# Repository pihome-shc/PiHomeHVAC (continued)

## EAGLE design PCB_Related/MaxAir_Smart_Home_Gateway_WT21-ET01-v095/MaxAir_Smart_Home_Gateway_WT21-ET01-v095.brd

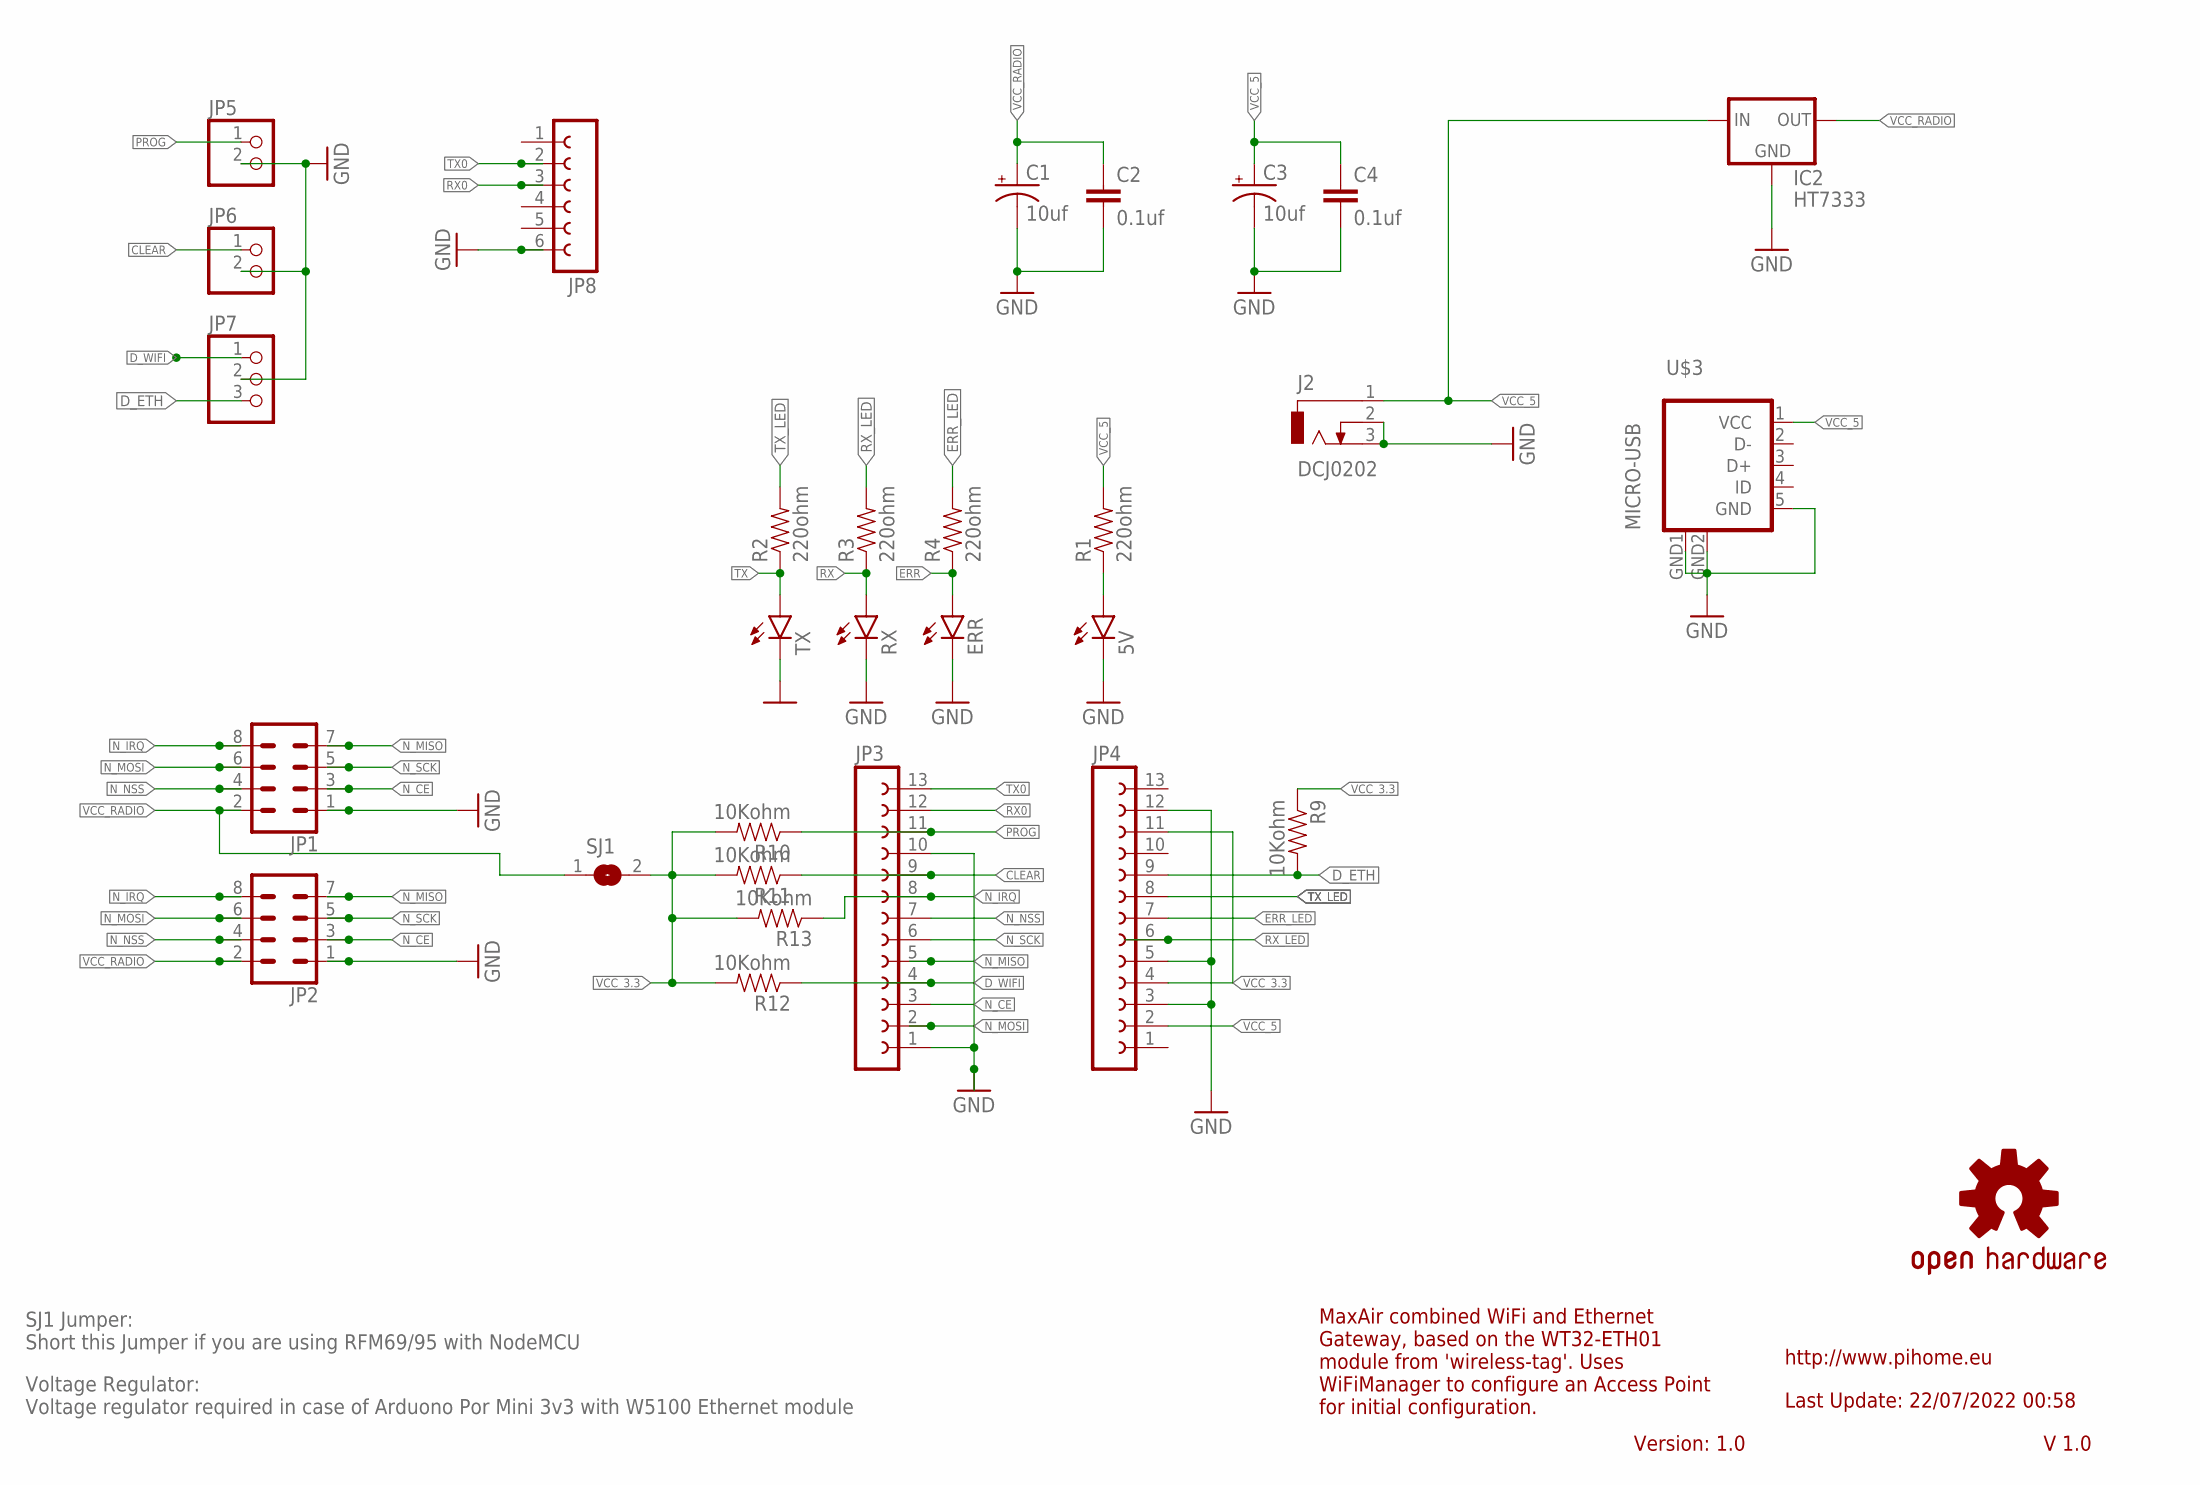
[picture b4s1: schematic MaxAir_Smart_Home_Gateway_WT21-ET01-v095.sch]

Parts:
5V: LED3MM
C1, C3: 10uf; CPOL-RADIAL-10UF-25V-KIT
C2, C4: 0.1uf; CAP-PTH-SMALL-KIT
ERR: LED3MM
IC2: HT7333; SOT-89
J2: DCJ0202
JP1, JP2: CONN_04X2; 2X4
JP3, JP4: FE13-1; FE13
JP5, JP6: PINHD-1X2; 1X02
JP7: PINHD-1X3; 1X03
JP8: FE06-1; FE06
LOGO1: OSHW-LOGOMINI; OSHW-LOGO-MINI
R1, R2, R3, R4: 220ohm; AXIAL-0.3
R9, R10, R11, R12, R13: 10Kohm; AXIAL-0.3
RX: LED3MM
SJ1: SJ
TX: LED3MM
U$3: MICRO-USB

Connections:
CLEAR: JP3.9, JP6.1, R11.P$1 (1)
D_ETH: JP4.9, JP7.3, R9.P$2 (2)
D_WIFI: JP3.4, JP7.1, R12.P$1 (1)
ERR: ERR.A, R4.P$1 (1)
ERR_LED: JP4.7, R4.P$2 (2)
GND: 5V.K (C), C1.2 (-), C2.2, C3.2 (-), C4.2, ERR.K (C), IC2.2 (GND), J2.2, J2.3, JP1.1, JP2.1, JP3.1, JP3.10, JP4.3, JP4.5, JP4.12, JP5.2, JP6.2, JP7.2, JP8.6, RX.K (C), TX.K (C), U$3.5 (GND), U$3.GND1 (GND), U$3.GND2 (GND)
unnamed: 5V.A, R1.P$1 (1)
N_CE: JP1.3, JP2.3, JP3.3
N_IRQ: JP1.8, JP2.8, JP3.8, R13.P$1 (1)
N_MISO: JP1.7, JP2.7, JP3.5
N_MOSI: JP1.6, JP2.6, JP3.2
N_NSS: JP1.4, JP2.4, JP3.7
N_SCK: JP1.5, JP2.5, JP3.6
PROG: JP3.11, JP5.1, R10.P$1 (1)
RX: R3.P$1 (1), RX.A
RX0: JP3.12, JP8.3
RX_LED: JP4.6, R3.P$2 (2)
TX: R2.P$1 (1), TX.A
TX0: JP3.13, JP8.2
TX_LED: JP4.8, R2.P$2 (2)
VCC_3.3: JP4.4, JP4.11, R9.P$1 (1), R10.P$2 (2), R11.P$2 (2), R12.P$2 (2), R13.P$2 (2), SJ1.2
VCC_5: C3.1 (+), C4.1, IC2.3 (IN), IC2.4 (IN), J2.1, JP4.2, R1.P$2 (2), U$3.1 (VCC)
VCC_RADIO: C1.1 (+), C2.1, IC2.1 (OUT), JP1.2, JP2.2, SJ1.1

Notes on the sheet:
http://www.pihome.eu
Last Update: 22/07/2022 00:58
MaxAir combined WiFi and Ethernet Gateway, based on the WT32-ETH01 module from 'wireless-tag'. Uses WiFiManager to configure an Access Point for initial configuration.
Version: 1.0
V 1.0
SJ1 Jumper: Short this Jumper if you are using RFM69/95 with NodeMCU
Voltage Regulator: Voltage regulator required in case of Arduono Por Mini 3v3 with W5100 Ethernet module

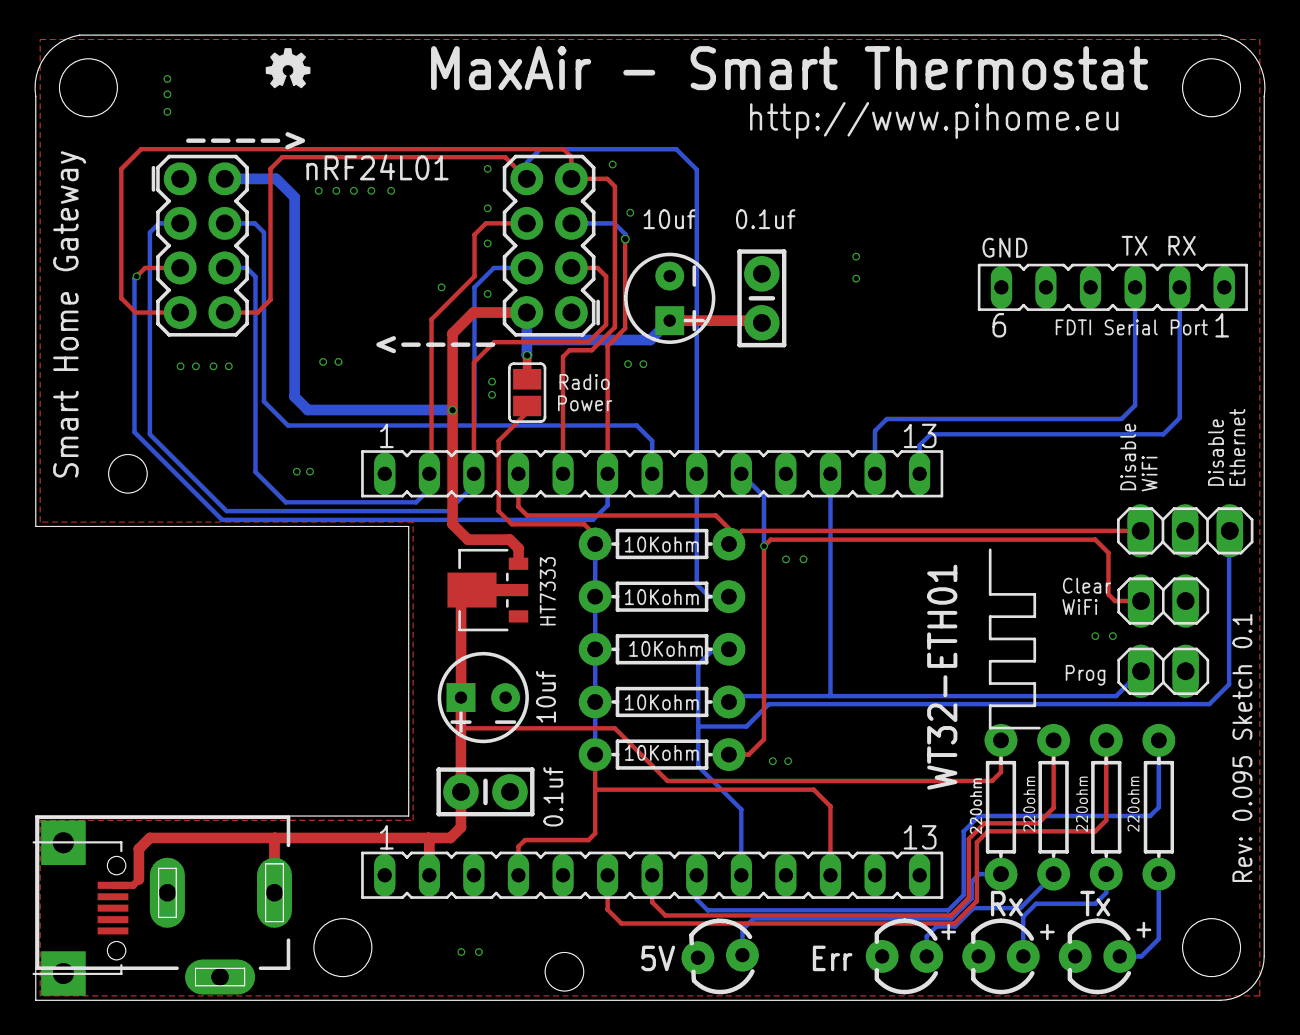
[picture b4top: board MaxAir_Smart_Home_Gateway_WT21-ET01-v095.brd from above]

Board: 2 copper layers, 70.1 x 55.0 mm, 34 parts (0 on the bottom side), 23 nets.

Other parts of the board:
U$1, U$2, U$4, U$5: STAND-OFF

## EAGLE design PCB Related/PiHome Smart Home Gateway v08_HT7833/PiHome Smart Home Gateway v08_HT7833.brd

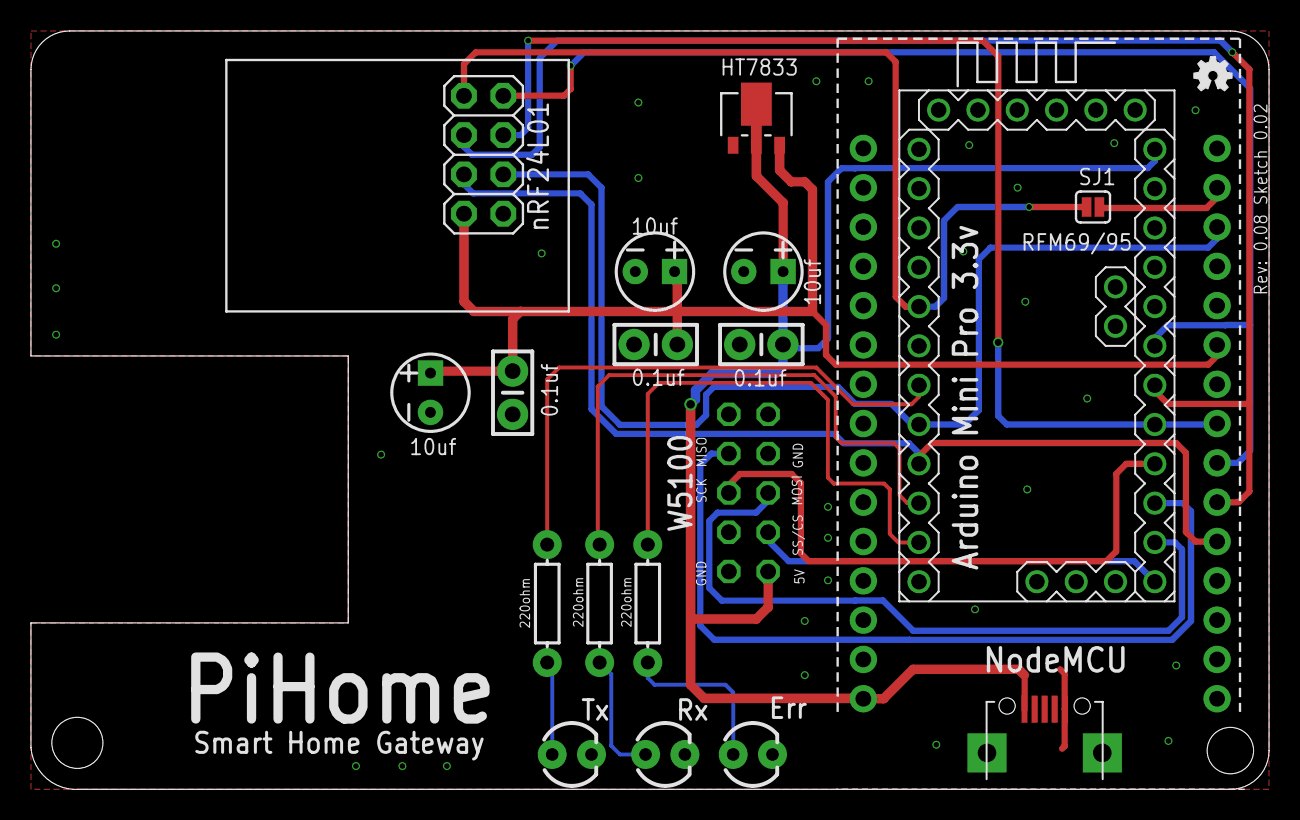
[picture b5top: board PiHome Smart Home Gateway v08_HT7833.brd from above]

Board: 2 copper layers, 80.0 x 49.0 mm, 22 parts (1 on the bottom side), 20 nets.

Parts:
C1, C5, C6: 10uf; CPOL-RADIAL-10UF-25V-KIT
C2, C3, C4: 0.1uf; CAP-PTH-SMALL-KIT
ERR: LED3MM
IC2: HT7333; SOT-89
JP1: 2X04
JP2, JP3: 1X15-CB
LOGO1: OSHW-LOGOMINI; OSHW-LOGO-MINI
M1: ARDUINO-PRO-MINI-3.3V; ARDUINO-PRO-MINI
R2, R3, R4: 220ohm; AXIAL-0.3
RX: LED3MM
SJ1: SOLDERJUMPERNC; SJ_2S
TX: LED3MM
U$2: STAND-OFF
U$3: MICRO-USB
W5100: 2X05

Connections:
ERR: ERR.A, R4.P$1
ERR_LED: M1.J7.2, R4.P$2
GND: C1.2, C2.2, C3.2, C4.2, C5.2, C6.2, ERR.K, IC2.2, JP1.1, JP2.10, JP2.14, JP3.7, JP3.14, M1.J3.1, M1.J6.2, M1.J7.9, RX.K, TX.K, U$3.5, U$3.GND1, U$3.GND2, W5100.1, W5100.8
IRQ: JP3.2, SJ1.1
N_CE: JP1.3, JP3.3, M1.J7.5
N_IRQ: JP1.8, M1.J7.8, SJ1.2
N_MISO: JP1.7, JP3.9, M1.J6.6
N_MOSI: JP1.6, JP3.10, M1.J6.7
N_NSS: JP1.4, JP3.11, M1.J7.4
N_SCK: JP1.5, JP3.8, M1.J6.8
RX: R3.P$1, RX.A
RX_LED: M1.J7.3, R3.P$2
TX: R2.P$1, TX.A
TX_LED: M1.J7.6, R2.P$2
VCC_3.3: C1.1, C2.1, C4.1, C6.1, IC2.1, JP1.2, JP3.6
VCC_5: C3.1, C5.1, IC2.3, IC2.4, JP2.15, M1.J6.1, U$3.1, W5100.2
W_MISO: M1.J6.10, W5100.7
W_MOSI: M1.J6.11, W5100.6
W_SCK: M1.J6.9, W5100.5
W_SS/CS: M1.J6.12, W5100.4

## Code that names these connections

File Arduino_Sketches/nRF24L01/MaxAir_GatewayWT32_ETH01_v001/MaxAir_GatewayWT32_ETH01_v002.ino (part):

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  //#define MY_RX_MESSAGE_BUFFER_FEATURE
  //#define MY_RX_MESSAGE_BUFFER_SIZE 5

  // We have to move CE/CSN pins for NRF radio
  #ifndef MY_RF24_CE_PIN
    #define MY_RF24_CE_PIN 4
  #endif
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
#if defined(PCB_VERSION_1)
  #define ETH_ONLY 35 // set LOW using jumper to only work in WIFI mode
  #define CLEAR_EEPROM 39 // set LOW using jumper to clear save WIFI credentials
  #define DISABLE_ETH 32 // set LOW using jumper to disable the Ethernet Interface
#else
  #define ADC_39 39 // used to determine if WiFi or Ethernet interfaces are disabled
  #define TRIGGER 5 // set LOW to indicate the relays are posotive level triggered
  #define CLEAR_EEPROM 32 // set LOW using jumper to clear save WIFI credentials (pin later used as i2c data)
#endif

#if defined(MY_USE_UDP)
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
void tick(){
  //toggle state
  int state = digitalRead(MY_DEFAULT_ERR_LED_PIN);  // get the current state of ERR LED pin
  digitalWrite(MY_DEFAULT_ERR_LED_PIN, !state);     // set pin to the opposite state
}

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        enable_eth = 0;
      }
    #else
      pinMode(TRIGGER, INPUT);

      // read ADC on pin 39
      int adc1 = analogRead(ADC_39);
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
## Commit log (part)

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2025-03-07 Create 300824
